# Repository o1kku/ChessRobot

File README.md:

# ChessRobot
This repository includes software, PCM model and other stuff for ChessRobot. ChessRobot is a tower crane like Robot that can move chesspieces without you having to move a finger! How cool is that :)

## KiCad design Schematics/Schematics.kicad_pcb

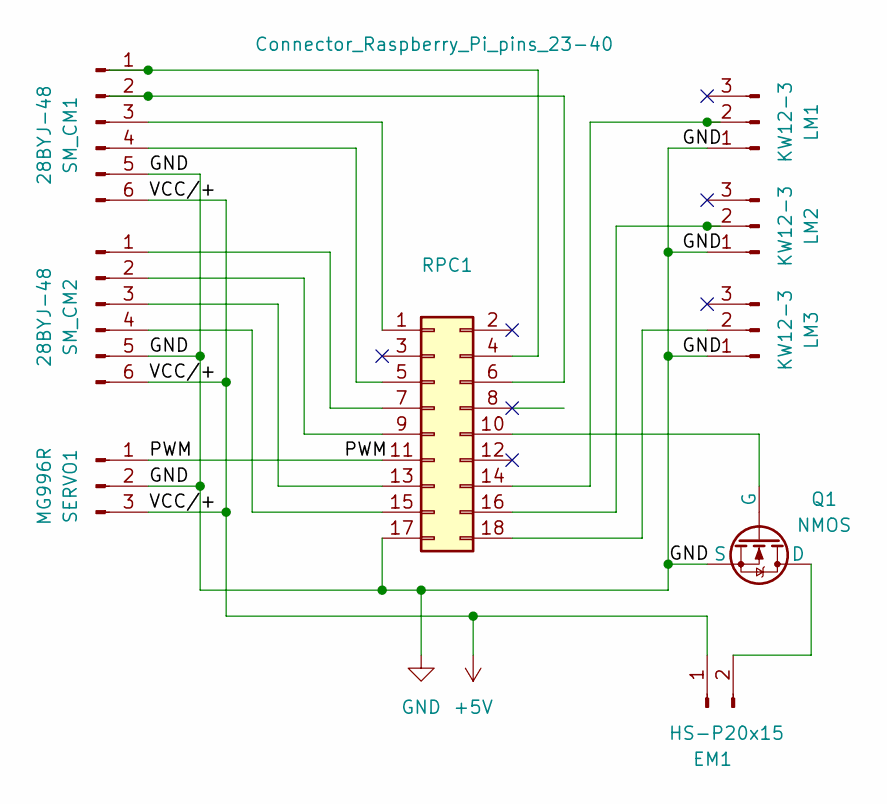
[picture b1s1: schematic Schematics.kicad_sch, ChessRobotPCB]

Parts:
EM1: HS-P20x15; PinSocket_1x02_P2.54mm_Vertical
LM1, LM2, LM3: KW12-3; PinSocket_1x03_P2.54mm_Vertical
Q1: NMOS; TO-220-3_Vertical
RPC1: Connector_Raspberry_Pi_pins_23-40; PinSocket_2x09_P2.54mm_Vertical
SERVO1: MG996R; PinSocket_1x03_P2.54mm_Vertical
SM_CM1, SM_CM2: 28BYJ-48; PinSocket_1x06_P2.54mm_Vertical

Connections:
+5V: EM1.1, SERVO1.3, SM_CM1.6, SM_CM2.6
/PWM: RPC1.11, SERVO1.1
GND: LM1.1, LM2.1, LM3.1, Q1.3 (S), RPC1.17, SERVO1.2, SM_CM1.5, SM_CM2.5
unnamed: EM1.2, Q1.1 (D)
unnamed: LM1.2, RPC1.14
unnamed: LM2.2, RPC1.16
unnamed: LM3.2, RPC1.18
unnamed: Q1.2 (G), RPC1.10
unnamed: RPC1.1, SM_CM1.3
unnamed: RPC1.4, SM_CM1.1
unnamed: RPC1.5, SM_CM1.4
unnamed: RPC1.6, SM_CM1.2
unnamed: RPC1.7, SM_CM2.1
unnamed: RPC1.9, SM_CM2.2
unnamed: RPC1.13, SM_CM2.3
unnamed: RPC1.15, SM_CM2.4

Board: 2 copper layers, 9 parts (0 on the bottom side), 16 nets, no tracks yet.

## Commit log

2026-03-07 gitignore generated for python / raspberry pi / KiCad project
2026-03-07 PCB model schematics created
2026-03-07 example code for controlling stepper motor
2026-03-08 GPIO pins updated, motors are functioning
2026-03-08 stepmotor class init
2026-03-08 Init class that controls stepper motor via ULN2003 driver
2026-03-08 Global configuration settings for the robot hardware
2026-03-08 init for more scalable structure of the project
2026-03-08 public method for rotating the motor a number of steps
2026-03-08 pin configs updated
2026-03-08 code for motor testing
2026-03-08 rotation direction fixed
2026-04-03 init comments
2026-04-03 class that reads limit switches implemented
2026-04-03 class that controls electromagnet via MOSFET switch implemented
2026-04-03 limit switch mock mode updated
2026-04-03 Implemented method that stops the motor when called.
2026-04-12 Minor typo / comment fixes, gitignore extended to include some Claude generated files
2026-04-12 tests added with pytest
2026-04-12 initial commit of a high-level chess robot controller -module
